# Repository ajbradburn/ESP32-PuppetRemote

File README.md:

The goal is to create a remote control for a puppet.

1. Direct communication between two ESP devices via ESP-NOW.
2. Playing sound upon trigger.
3. Control servo to articulate eye lids.
4. Control motor to retract wings.

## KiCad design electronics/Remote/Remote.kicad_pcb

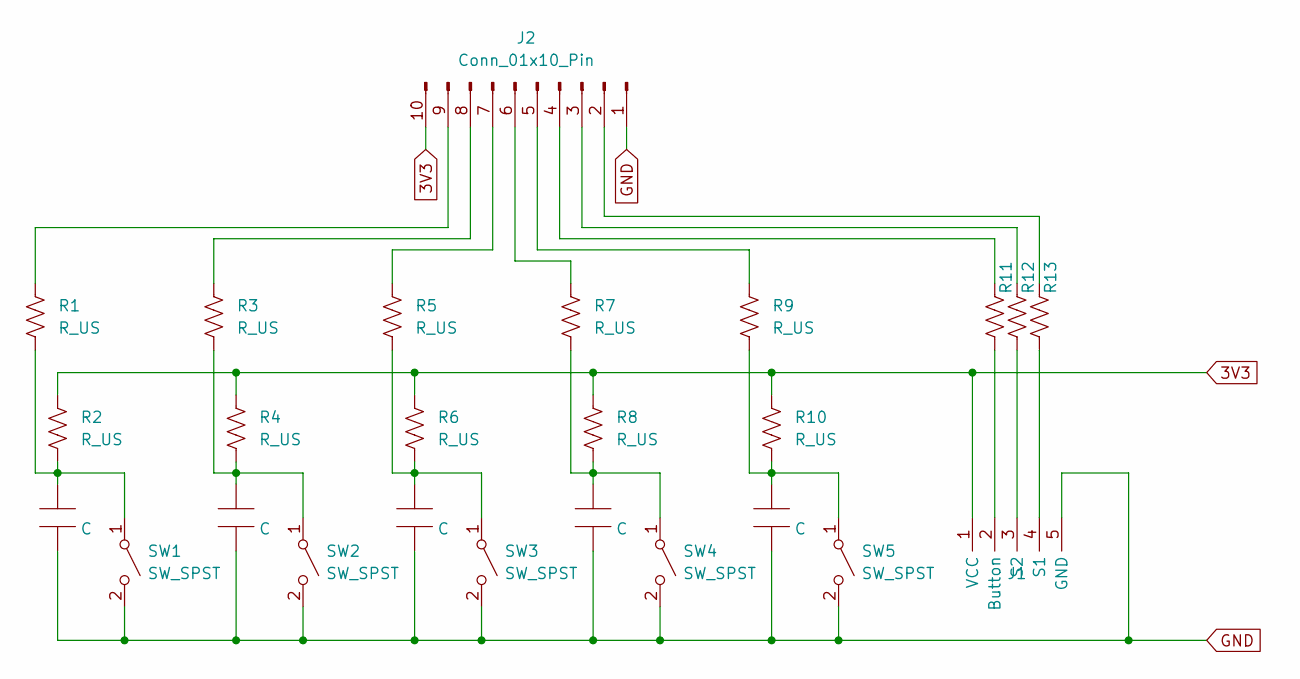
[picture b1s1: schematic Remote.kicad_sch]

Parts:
C1, C2, C3, C4, C5: C; C_MicroMELF_MMU-0102
J1: PinHeader_1x05_P2.54mm_Vertical
J2: Conn_01x10_Pin; PinHeader_1x10_P2.54mm_Vertical
R1, R2, R3, R4, R5, R6, R7, R8, R9, R10, R11, R12, R13: R_US; R_0805_2012Metric
SW1, SW2, SW3, SW4, SW5: SW_SPST; SW_Push_1P1T_NO_6x6mm

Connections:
3V3: J1.1 (VCC), J2.10, R2.1, R4.1, R6.1, R8.1, R10.1
GND: C1.1, C2.1, C3.1, C4.1, C5.1, J1.5 (GND), J2.1, SW1.2 (B), SW2.2 (B), SW3.2 (B), SW4.2 (B), SW5.2 (B)
unnamed: J1.2 (Button), R11.2
unnamed: J1.4 (S1), R13.2
unnamed: J1.3 (S2), R12.2
unnamed: J2.2, R13.1
unnamed: J2.3, R12.1
unnamed: J2.4, R11.1
unnamed: J2.5, R9.1
unnamed: J2.6, R7.1
unnamed: J2.7, R5.1
unnamed: J2.8, R3.1
unnamed: J2.9, R1.1
unnamed: C1.2, R1.2, R2.2, SW1.1 (A)
unnamed: C2.2, R3.2, R4.2, SW2.1 (A)
unnamed: C3.2, R5.2, R6.2, SW3.1 (A)
unnamed: C4.2, R7.2, R8.2, SW4.1 (A)
unnamed: C5.2, R9.2, R10.2, SW5.1 (A)

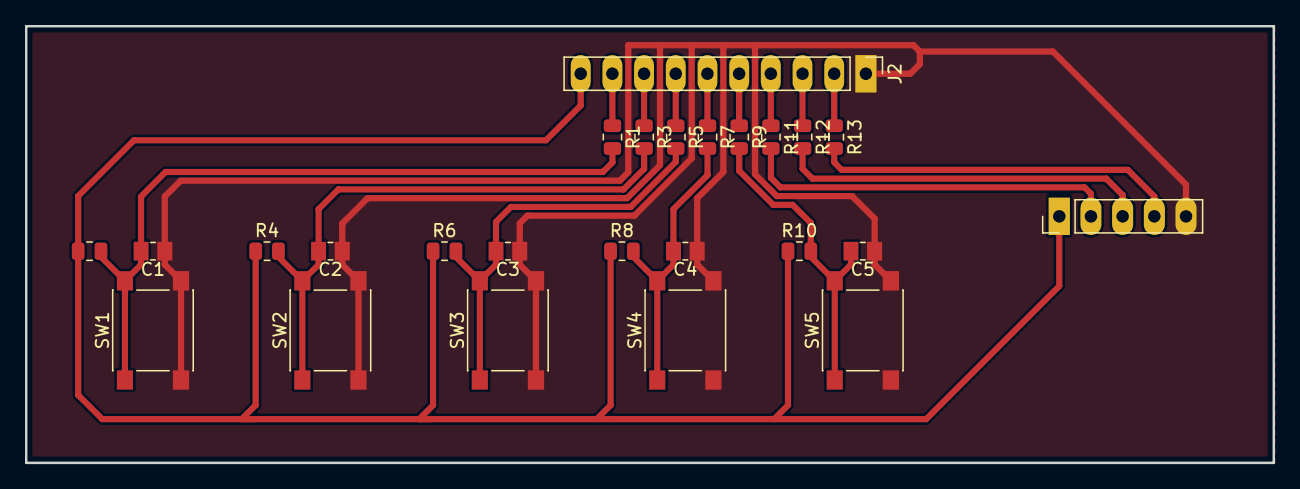
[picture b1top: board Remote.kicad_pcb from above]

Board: 2 copper layers, 100.0 x 35.0 mm, 25 parts (0 on the bottom side), 18 nets.

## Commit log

2024-02-28 First commit.
2024-02-28 ESP-Now test sketches implemented.
2024-02-28 Added a line to increase the volume of the audio.
2024-02-29 I have a working servo and motor control.
2024-02-29 A working proof of concept for everything.
2024-02-29 Added an electronics folder.
2024-02-29 Added a schematic for a basic button board.
2024-03-01 Created the basic remote control functionality.
2024-03-01 I have a mostly working receiver. I need to sort out audio playback. Wifi is enabled with ESPNow, and I think that might be the cause of this issue. I'll do some testing.
2024-03-02 I have a working proof-of-concept for the remote control. There is a bug I've identified. Something about initializing I2C, and then assigning a variable afterwards causes issues with I2S output. Add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
    Right now, the variable is calling a servo object from a 3rd
    party library, but that isn't important. making my own function, and
    calling that function will produce the same result.
2024-03-02 Working on making a script that can be submitted as part of a bug report.
2024-03-02 sound_test.py is a stripped down demonstration of the bug.
2024-03-02 Two stripped down examples of the bug, one with blocking, the other with non-blocking implimentation.
2024-03-03 A functional, non-blocking implementation.
2024-03-03 Fixed some issues with the flap or blink function being called before a previous operation was called.
2024-03-03 Basic remote button interface created.
2024-03-03 Added some dragon sounds.
2024-03-06 Added a circuit schematic for the receiver/controller of electronics.
